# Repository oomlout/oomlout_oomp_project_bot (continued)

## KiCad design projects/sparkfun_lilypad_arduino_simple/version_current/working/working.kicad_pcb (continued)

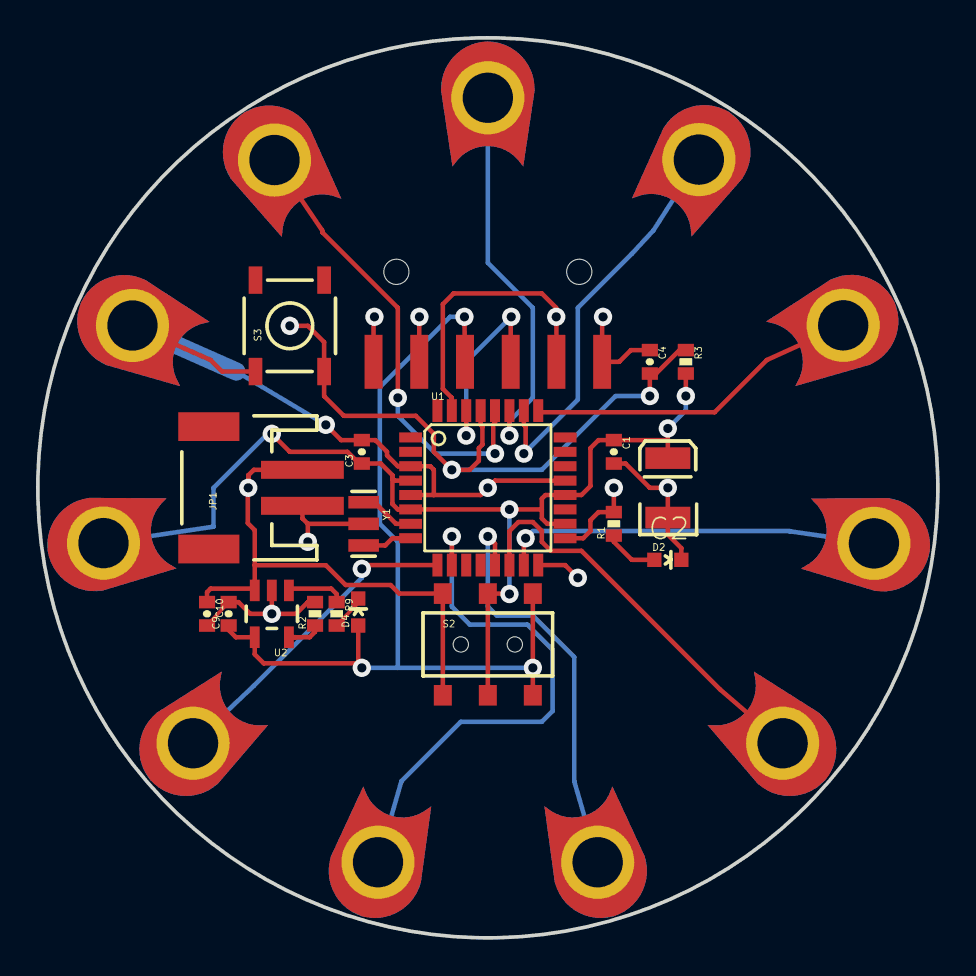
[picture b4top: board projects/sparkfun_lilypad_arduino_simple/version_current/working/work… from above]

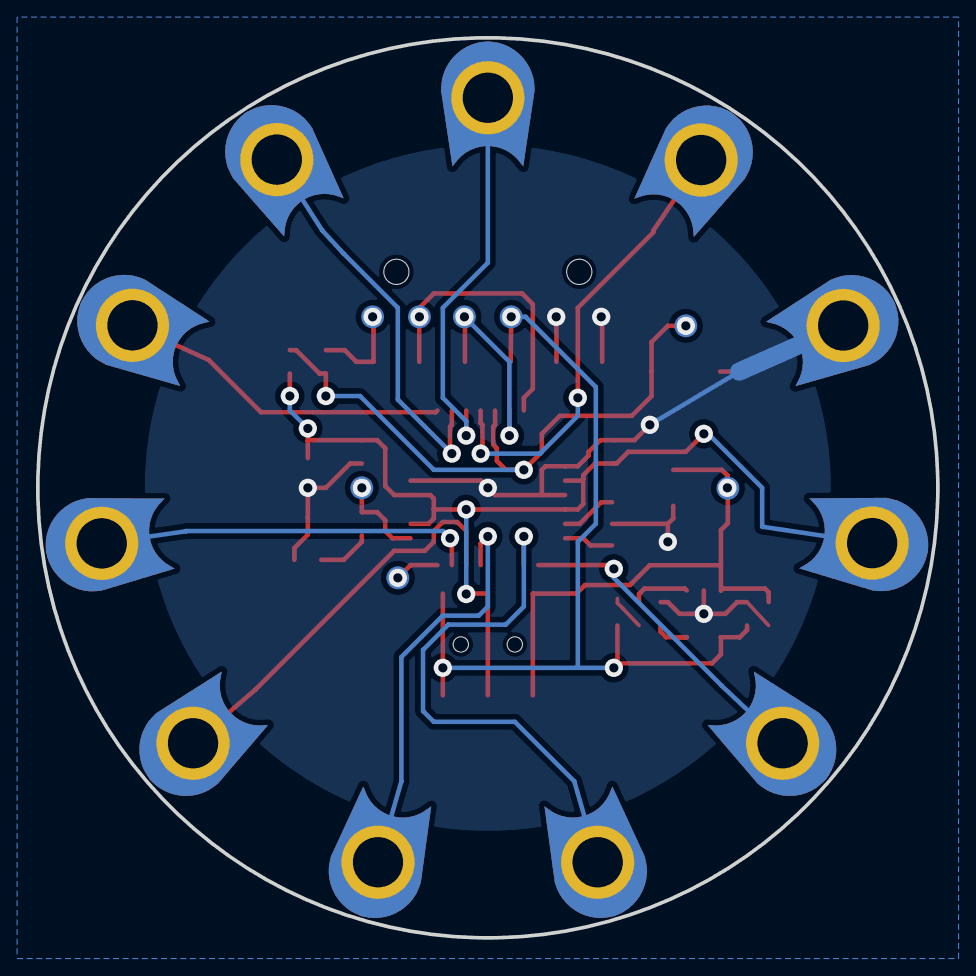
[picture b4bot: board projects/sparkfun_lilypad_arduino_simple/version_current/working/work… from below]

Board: 2 copper layers, 50.0 x 50.0 mm, 38 parts (8 on the bottom side), 25 nets.

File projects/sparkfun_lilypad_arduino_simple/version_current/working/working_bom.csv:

"Id";"Designator";"Footprint";"Quantity";"Designation";"Supplier and ref";
1;"Y1";"RESONATOR-SMD";1;"8MHz";;;
2;"A3/17,U$37,U$45,U$39,U$4,A4/18,U$41,A2/16,U$43,U$35,A5/19";"PETAL-LONG-1-2SIDE";11;"SEWTAP9";;;
3;"D2";"LED-0603";1;"Status";;;
4;"S2";"AYZ0202";1;"On/Off";;;
5;"C1,C4";"0402-CAP";2;"0.1uF";;;
6;"JP2";"1X06-SMD";1;"";;;
7;"U2";"SOT23-5";1;"MCP73831";;;
8;"D4";"LED-0603";1;"Yellow";;;
9;"C10,C9";"0402-CAP";2;"4.7uF";;;
10;"U1";"TQFP32-08";1;"ATMEGA328";;;
11;"JP1";"JST-2-SMD";1;"LiPo";;;
12;"R9,R1";"0402-RES";2;"330";;;
13;"C3";"0402-CAP";1;"1.0uF";;;
14;"R2";"0402-RES";1;"10k";;;
15;"S3";"TACTILE_SWITCH_SMD";1;"Reset";;;
16;"R3";"0402-RES";1;"10K";;;
17;"C2";"EIA3528";1;"47uF";;;
18;"TP-FTDI_VCC0,PP-MISO0,TP-DTR0,PP-RST0,TP-TX0,PP-SCK0,TP-VBATT0,TP-RX0";"PAD.03X.05";8;"";;;

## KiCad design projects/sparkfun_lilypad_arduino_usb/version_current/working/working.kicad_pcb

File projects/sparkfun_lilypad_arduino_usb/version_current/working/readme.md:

# OOMP Project  
## LilyPad_Arduino_USB  by sparkfun  
  
oomp key: oomp_projects_flat_sparkfun_lilypad_arduino_usb  
(snippet of original readme)  
  
LilyPad Arduino USB  
===================  
  
[    
*LilyPad Arduino USB (DEV-11990)*](https://www.sparkfun.com/products/11190)  
  
The LilyPad Arduino USB is a sewable Arduino compatible board with a built-in LiPo battery charger. It connects via microUSB cable to your computer, which means that, unlike regular LilyPad boards, it needs no external hardware to be programmed.   
  
As of Arduino release 1.0.2, the LilyPad Arduino USB is supported as a native board- no additional files needed!  
  
Firmware was compiled in WinAVR-20100110.    
Hardware was developed in EAGLE 6.3.0.  
  
License Information  
-------------------  
The hardware design is released under [CC-SA v3 license](http://creativecommons.org/licenses/by-sa/3.0/us/).  
  
The firmware is released under a modified beerware license, allowing for the purchase of any libation, alcoholic or non.  

  full source readme at [readme_src.md](readme_src.md)  
  
source repo at: [https://github.com/sparkfun/LilyPad_Arduino_USB](https://github.com/sparkfun/LilyPad_Arduino_USB)  
## Board  

## Schematic  

[schematic pdf](working_schematic.pdf)  
## Images

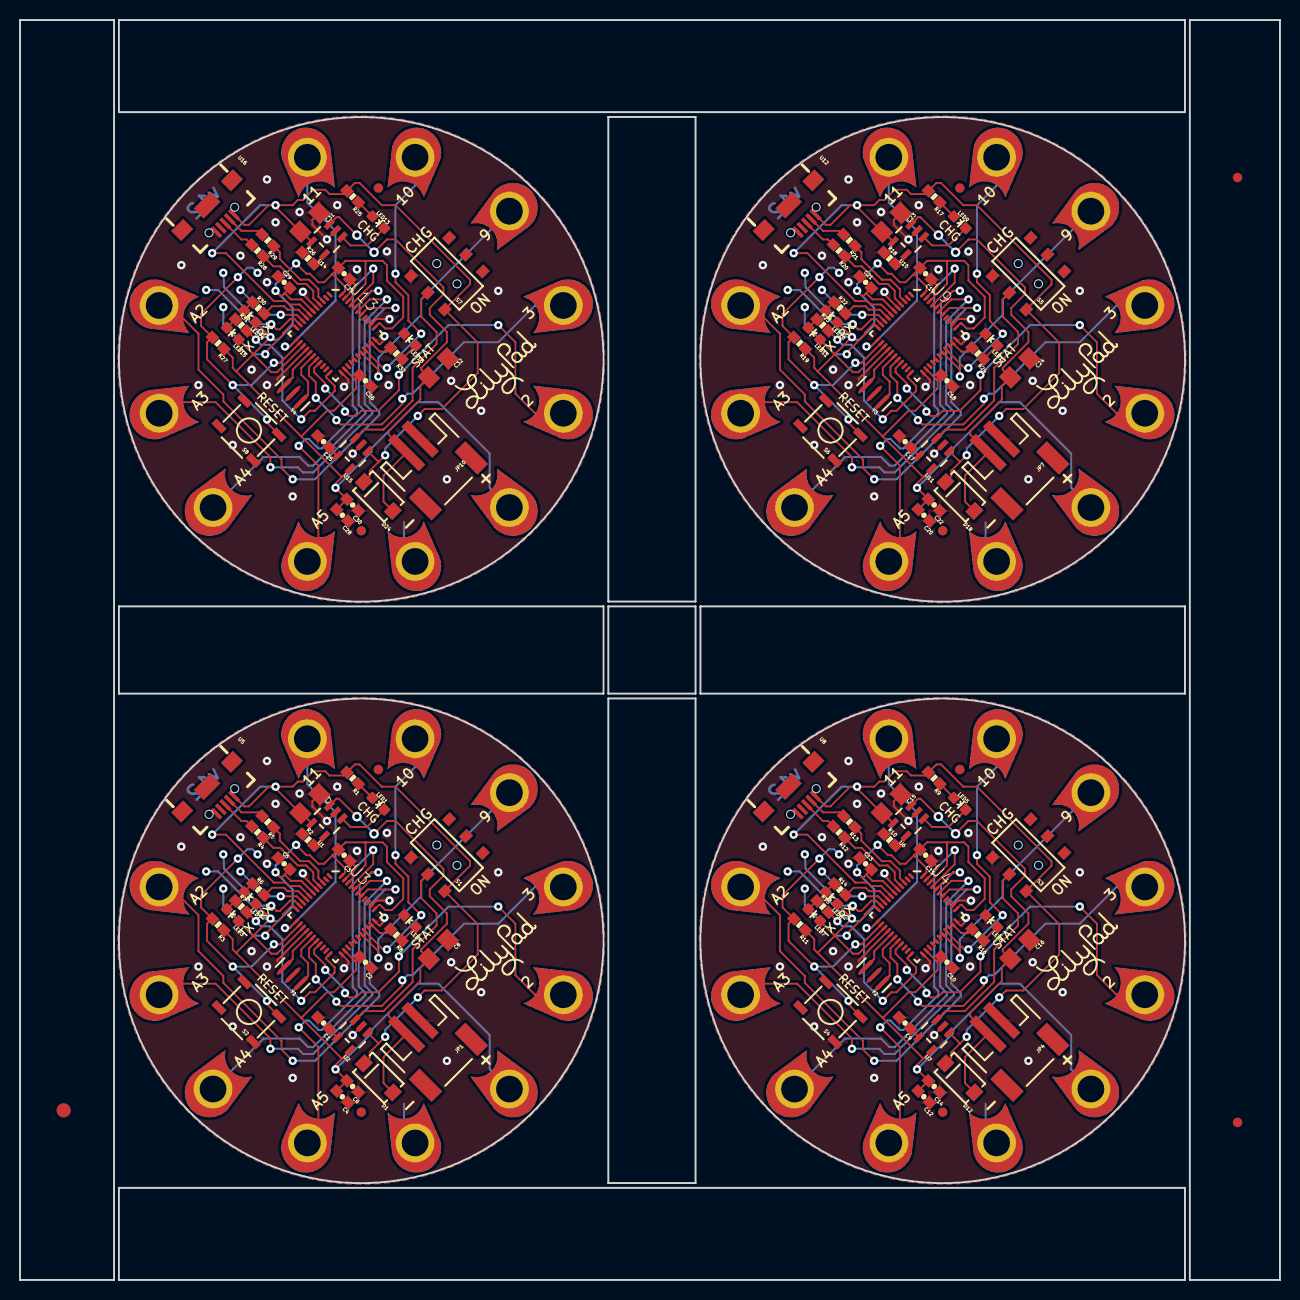
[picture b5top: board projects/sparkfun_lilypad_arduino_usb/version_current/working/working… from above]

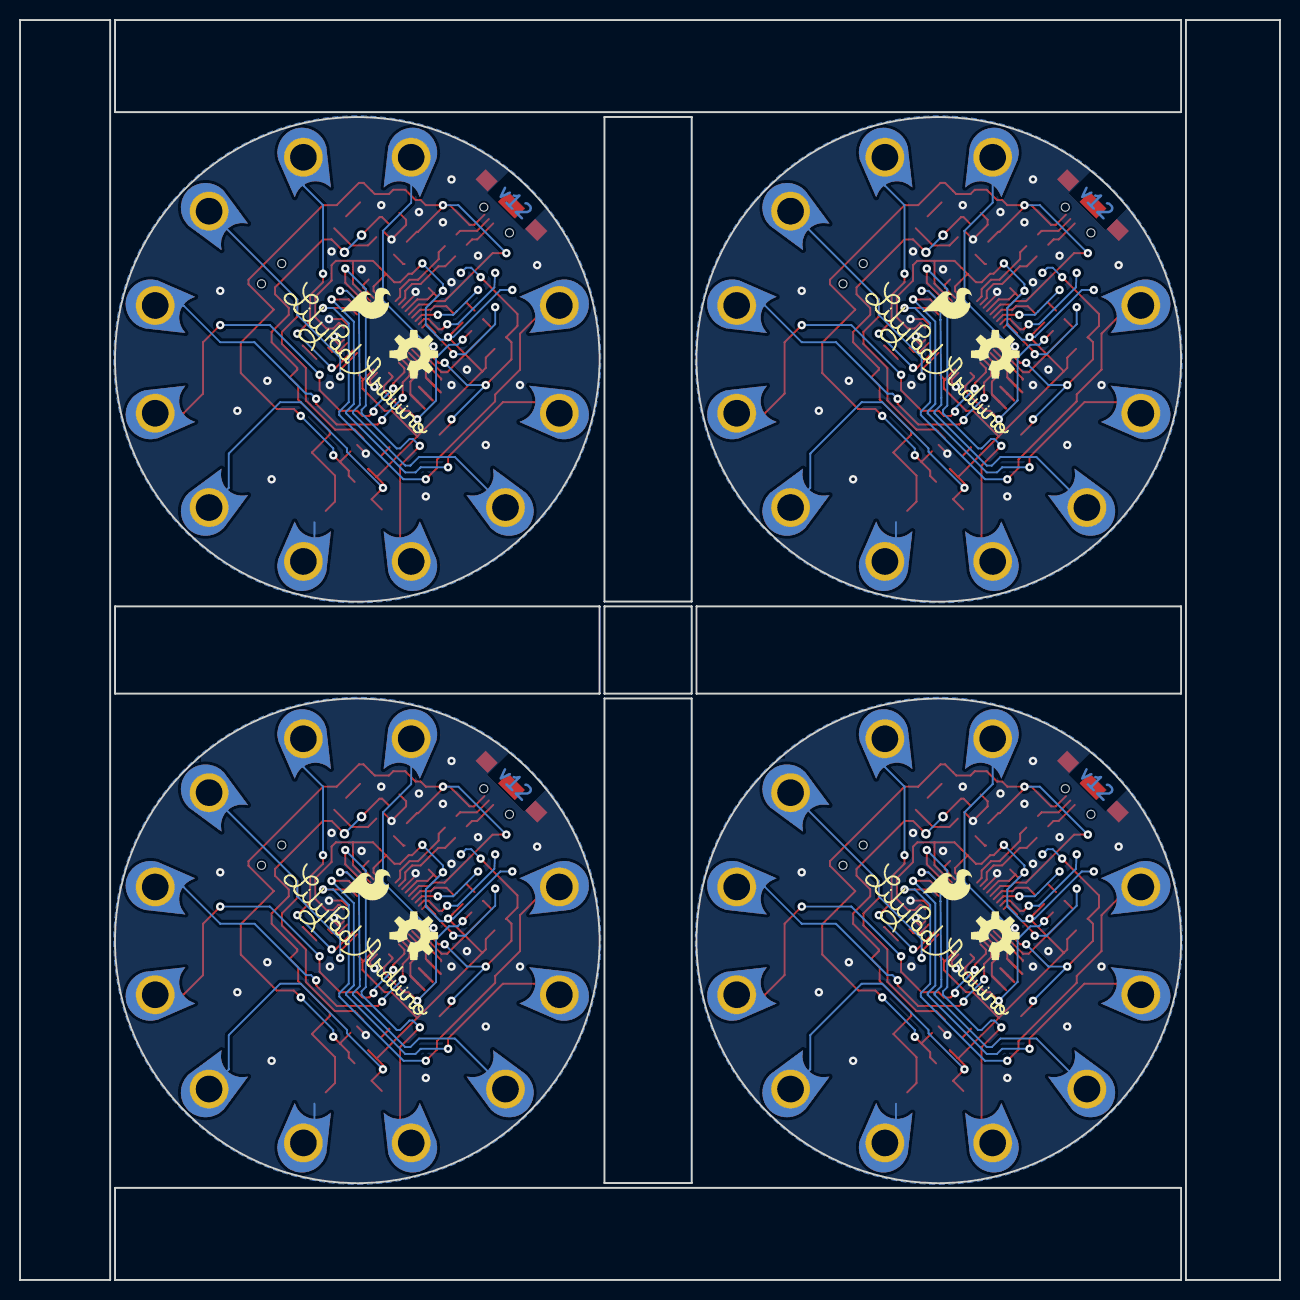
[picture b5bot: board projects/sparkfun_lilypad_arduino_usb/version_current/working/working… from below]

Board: 4 copper layers, 132.1 x 132.1 mm, 187 parts (12 on the bottom side), 124 nets.

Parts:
+0, +1, +2, +3: SEWTAP9; PETAL-LONG-1-2SIDE
-0, -1, -2, -3: SEWTAP9; PETAL-LONG-1-2SIDE
A1, A2, A3, A4, A5, A6, A7, A8, A9, A10, A11, A12, A13, A14, A15, A16: SEWTAP9; PETAL-LONG-1-2SIDE
C1, C9, C17, C25: 470pF; 0603-CAP
C2, C3, C4, C10, C11, C12, C18, C19, C20, C26, C27, C28: .1uF; 0603-CAP
C5, C13, C21, C29: 1uF; 0603-CAP
C6, C14, C22, C30: 4.7uF; 0603-CAP
C7, C8, C15, C16, C23, C24, C31, C32: 4.7uF; 1206
D1, D12, D18, D24: B340A; SMA-DIODE
D2, D3, D4, D5, D6, D7, D8, D9, D10, D11, D13, D14, D15, D16, D17, D19, D20, D21, D22, D23: SEWTAP9; PETAL-LONG-1-2SIDE
E$1: FIDUCIAL-1.5X3
E$3, E$5: FIDUCIAL-1X2
JP1, JP4, JP7, JP10: JST-2; JST-2-SMD
JP2, JP3, JP5, JP6, JP8, JP9, JP11, JP12: FIDUCIAL1X2; FIDUCIAL-1X2
LED1, LED2, LED3, LED4, LED5, LED6, LED7, LED8, LED9, LED10, LED11, LED12, LED13, LED14, LED15, LED16: RED; LED-0603
R1, R6, R7, R8, R9, R14, R15, R16, R17, R22, R23, R24, R25, R30, R31, R32: 330; 0603-RES
R2, R3, R10, R11, R18, R19, R26, R27: 10k; 0603-RES
R4, R5, R12, R13, R20, R21, R28, R29: 22; 0603-RES
S1, S3, S5, S7: DPDT; AYZ0202
S2, S4, S6, S8: !RESET; TACTILE_SWITCH_SMD
U1, U6, U10, U14: MCP73831; SOT23-5
U2, U7, U11, U15: MIC5219 3.3V; SOT23-5
U3, U4, U9, U13: ATMEGA32U41:1-LESS_PASTE; QFN-44-NOPAD_1_1-LESS_PASTE
U5, U8, U12, U16: USB-AB-MICRO-SMD_V03
U$1, U$3, U$9, U$14: LOGO-LPLPA; LOGO-LPA
U$2, U$8, U$12, U$13: LOGO-LPLP; LOGO-LILYPAD
U$4, U$5, U$10, U$15: OSHW-LOGOM; OSHW-LOGO-M
U$6, U$7, U$11, U$16: SFE_LOGO_FLAME_.2
Y1, Y2, Y3, Y4: 8MHZ; RESONATOR-SMD

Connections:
3.3V: +0.1, C2.2, C3.2, C4.2, C5.2, C6.2, LED2.A, LED3.A, R3.1, U2.5, U3.6, U3.14, U3.24, U3.34, U3.42, U3.44
3.3V1: +1.1, C10.2, C11.2, C12.2, C13.2, C14.2, LED6.A, LED7.A, R11.1, U4.6, U4.14, U4.24, U4.34, U4.42, U4.44, U7.5
3.3V2: +2.1, C18.2, C19.2, C20.2, C21.2, C22.2, LED10.A, LED11.A, R19.1, U9.6, U9.14, U9.24, U9.34, U9.42, U9.44, U11.5
3.3V3: +3.1, C26.2, C27.2, C28.2, C29.2, C30.2, LED14.A, LED15.A, R27.1, U13.6, U13.14, U13.24, U13.34, U13.42, U13.44, U15.5
5V: C7.2, D1.C, R1.2, S1.1, U1.4, U2.1, U3.7, U5.VBUS1
5V1: C15.2, D12.C, R9.2, S3.1, U4.7, U6.4, U7.1, U8.VBUS1
5V2: C23.2, D18.C, R17.2, S5.1, U9.7, U10.4, U11.1, U12.VBUS1
5V3: C31.2, D24.C, R25.2, S7.1, U13.7, U14.4, U15.1, U16.VBUS1
D+: R4.1, U3.4
D+1: R12.1, U4.4
D+2: R20.1, U9.4
D+3: R28.1, U13.4
D-: R5.1, U3.3
D-1: R13.1, U4.3
D-2: R21.1, U9.3
D-3: R29.1, U13.3
GND: -0.1, C1.2, C2.1, C3.1, C4.1, C5.1, C6.1, C7.1, C8.1, JP1.1, LED4.C, R2.1, S1.3, S2.1, U1.2, U2.2, U3.5, U3.15, U3.23, U3.33, U3.35, U3.43, U5.GND1, Y1.2
GND1: -1.1, C9.2, C10.1, C11.1, C12.1, C13.1, C14.1, C15.1, C16.1, JP4.1, LED8.C, R10.1, S3.3, S4.1, U4.5, U4.15, U4.23, U4.33, U4.35, U4.43, U6.2, U7.2, U8.GND1, Y2.2
GND2: -2.1, C17.2, C18.1, C19.1, C20.1, C21.1, C22.1, C23.1, C24.1, JP7.1, LED12.C, R18.1, S5.3, S6.1, U9.5, U9.15, U9.23, U9.33, U9.35, U9.43, U10.2, U11.2, U12.GND1, Y3.2
GND3: -3.1, C25.2, C26.1, C27.1, C28.1, C29.1, C30.1, C31.1, C32.1, JP10.1, LED16.C, R26.1, S7.3, S8.1, U13.5, U13.15, U13.23, U13.33, U13.35, U13.43, U14.2, U15.2, U16.GND1, Y4.2
unnamed: LED2.C, R6.1
unnamed: S1.2, U2.3
unnamed: LED1.A, R1.1
unnamed: LED1.C, U1.1
unnamed: U3.17, Y1.1
unnamed: R2.2, U1.5
unnamed: U3.16, Y1.3
unnamed: C1.1, U2.4
unnamed: D11.1, U3.12
unnamed: D10.1, U3.30
unnamed: D9.1, U3.29
unnamed: D5.1, U3.19
unnamed: D6.1, U3.18
unnamed: A5.1, U3.41
unnamed: A4.1, U3.40
unnamed: A3.1, U3.39
unnamed: A2.1, U3.38
unnamed: LED4.A, R8.1
unnamed: R5.2, U5.D-1
unnamed: R4.2, U5.D+1
unnamed: LED3.C, R7.1
unnamed: S3.2, U7.3
unnamed: LED5.A, R9.1
unnamed: LED5.C, U6.1
unnamed: R10.2, U6.5
unnamed: C9.1, U7.4
unnamed: D8.1, U4.12
unnamed: D7.1, U4.30
unnamed: D3.1, U4.29
unnamed: A7.1, U4.41
unnamed: A8.1, U4.40
unnamed: A6.1, U4.39
unnamed: A1.1, U4.38
unnamed: R13.2, U8.D-1
unnamed: R12.2, U8.D+1
unnamed: LED6.C, R14.1
unnamed: LED7.C, R15.1
unnamed: U4.17, Y2.1
unnamed: U4.16, Y2.3
unnamed: D2.1, U4.19
unnamed: D4.1, U4.18
unnamed: LED8.A, R16.1
unnamed: S5.2, U11.3
unnamed: LED9.A, R17.1
unnamed: LED9.C, U10.1
unnamed: R18.2, U10.5
unnamed: C17.1, U11.4
unnamed: D17.1, U9.12
unnamed: D16.1, U9.30
unnamed: D14.1, U9.29
unnamed: A11.1, U9.41
unnamed: A12.1, U9.40
unnamed: A10.1, U9.39
unnamed: A9.1, U9.38
unnamed: R21.2, U12.D-1
unnamed: R20.2, U12.D+1
unnamed: LED10.C, R22.1
unnamed: LED11.C, R23.1
unnamed: U9.17, Y3.1
unnamed: U9.16, Y3.3
unnamed: D13.1, U9.19
unnamed: D15.1, U9.18
unnamed: LED12.A, R24.1
unnamed: S7.2, U15.3
unnamed: LED13.A, R25.1
unnamed: LED13.C, U14.1
unnamed: R26.2, U14.5
unnamed: C25.1, U15.4
unnamed: D23.1, U13.12
unnamed: D22.1, U13.30
unnamed: D20.1, U13.29
unnamed: A15.1, U13.41
unnamed: A16.1, U13.40
unnamed: A14.1, U13.39
unnamed: A13.1, U13.38
unnamed: R29.2, U16.D-1
unnamed: R28.2, U16.D+1
unnamed: LED14.C, R30.1
unnamed: LED15.C, R31.1
unnamed: U13.17, Y4.1
unnamed: U13.16, Y4.3
unnamed: D19.1, U13.19
unnamed: D21.1, U13.18
unnamed: LED16.A, R32.1
RESET: R3.2, S2.3, U3.13
RESET1: R11.2, S4.3, U4.13
RESET2: R19.2, S6.3, U9.13
RESET3: R27.2, S8.3, U13.13
RX_LED: R6.2, U3.8
RX_LED1: R14.2, U4.8
RX_LED2: R22.2, U9.8
RX_LED3: R30.2, U13.8
TX_LED: R7.2, U3.22
TX_LED1: R15.2, U4.22
TX_LED2: R23.2, U9.22
TX_LED3: R31.2, U13.22
USER_LED: R8.2, U3.32
USER_LED1: R16.2, U4.32
USER_LED2: R24.2, U9.32
USER_LED3: R32.2, U13.32
V_BATT: C8.2, D1.A, JP1.2, U1.3
V_BATT1: C16.2, D12.A, JP4.2, U6.3
V_BATT2: C24.2, D18.A, JP7.2, U10.3
V_BATT3: C32.2, D24.A, JP10.2, U14.3

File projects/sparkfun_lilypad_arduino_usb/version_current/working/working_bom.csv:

"Id";"Designator";"Footprint";"Quantity";"Designation";"Supplier and ref";
1;"R23,R8,R24,R25,R31,R7,R6,R14,R22,R9,R15,R1,R32,R17,R30,R16";"0603-RES";16;"330";;;
2;"LED8,LED5,LED15,LED3,LED2,LED10,LED4,LED6,LED13,LED14,LED9,LED11,LED1,LED16,LED12,LED7";"LED-0603";16;"RED";;;
3;"A13,D23,D10,A7,D17,D5,-3,+1,+0,A3,D6,-0,A9,A10,D4,-2,D13,A16,D8,+3,D19,A1,A2,A12,A5,A6,A4,D16,D15,A11,D3,-1,D7,D2,D11,+2,D21,D14,D22,A8,A15,D9,D20,A14";"PETAL-LONG-1-2SIDE";44;"SEWTAP9";;;
4;"JP1,JP4,JP10,JP7";"JST-2-SMD";4;"JST-2";;;
5;"JP9,JP8,JP5,JP2,JP6,JP3,JP11,JP12";"FIDUCIAL-1X2";8;"FIDUCIAL1X2";;;
6;"C32,C7,C16,C23,C15,C8,C31,C24";"1206";8;"4.7uF";;;
7;"C10,C28,C4,C3,C27,C20,C12,C26,C2,C18,C11,C19";"0603-CAP";12;".1uF";;;
8;"S8,S6,S4,S2";"TACTILE_SWITCH_SMD";4;"!RESET";;;
9;"C22,C6,C14,C30";"0603-CAP";4;"4.7uF";;;
10;"U$13,U$2,U$12,U$8";"LOGO-LILYPAD";4;"LOGO-LPLP";;;
11;"R20,R13,R12,R5,R21,R28,R29,R4";"0603-RES";8;"22";;;
12;"D24,D12,D1,D18";"SMA-DIODE";4;"B340A";;;
13;"C29,C5,C21,C13";"0603-CAP";4;"1uF";;;
14;"U8,U5,U12,U16";"USB-AB-MICRO-SMD_V03";4;"";;;
15;"R18,R2,R19,R10,R3,R11,R27,R26";"0603-RES";8;"10k";;;
16;"E$3,E$5";"FIDUCIAL-1X2";2;"";;;
17;"U7,U15,U11,U2";"SOT23-5";4;"MIC5219 3.3V";;;
18;"S1,S3,S7,S5";"AYZ0202";4;"DPDT";;;
19;"C9,C25,C17,C1";"0603-CAP";4;"470pF";;;
20;"U13,U9,U3,U4";"QFN-44-NOPAD_1_1-LESS_PASTE";4;"ATMEGA32U41:1-LESS_PASTE";;;
21;"U1,U10,U6,U14";"SOT23-5";4;"MCP73831";;;
22;"E$1";"FIDUCIAL-1.5X3";1;"";;;
23;"Y1,Y3,Y2,Y4";"RESONATOR-SMD";4;"8MHZ";;;
24;"U$6,U$16,U$7,U$11";"SFE_LOGO_FLAME_.2";4;"";;;
25;"U$4,U$5,U$15,U$10";"OSHW-LOGO-M";4;"OSHW-LOGOM";;;
26;"U$14,U$3,U$1,U$9";"LOGO-LPA";4;"LOGO-LPLPA";;;

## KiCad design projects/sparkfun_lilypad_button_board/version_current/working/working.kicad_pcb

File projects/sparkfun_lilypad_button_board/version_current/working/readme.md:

# OOMP Project  
## LilyPad_Button_Board  by sparkfun  
  
oomp key: oomp_projects_flat_sparkfun_lilypad_button_board  
(snippet of original readme)  
  
SparkFun LilyPad Button Board  
========================================  

[*SparkFun LilyPad Button Board (DEV-08776)*](https://www.sparkfun.com/products/8776)  
  
We designed this board to give the user a low profile button without any sharp edges.   
Button closes when you push it and opens when you release (momentary push button).  
  
Repository Contents  
-------------------  
* **/Hardware** - All Eagle design files (.brd, .sch)  
  
Documentation  
-------------------  
* **[Hookup Guide](https://learn.sparkfun.com/tutorials/lilypad-buttons-and-switches)**  
  
License Information  
-------------------  
  
This product is _**open source**_!   
  
Please review the LICENSE.md file for license information.   
  
If you have any questions or concerns on licensing, please contact techsupport@sparkfun.com.  
  
Distributed as-is; no warranty is given.  
  
- Your friends at SparkFun.  
  
_<COLLABORATION CREDIT>_  
  
_Note: A portion of this sale is given back to Dr. Leah Buechley for continued development and education of e-textiles._  
  
  full source readme at [readme_src.md](readme_src.md)  
  
source repo at: [https://github.com/sparkfun/LilyPad_Button_Board](https://github.com/sparkfun/LilyPad_Button_Board)  
## Board  

## Schematic  

[schematic pdf](working_schematic.pdf)  
## Images

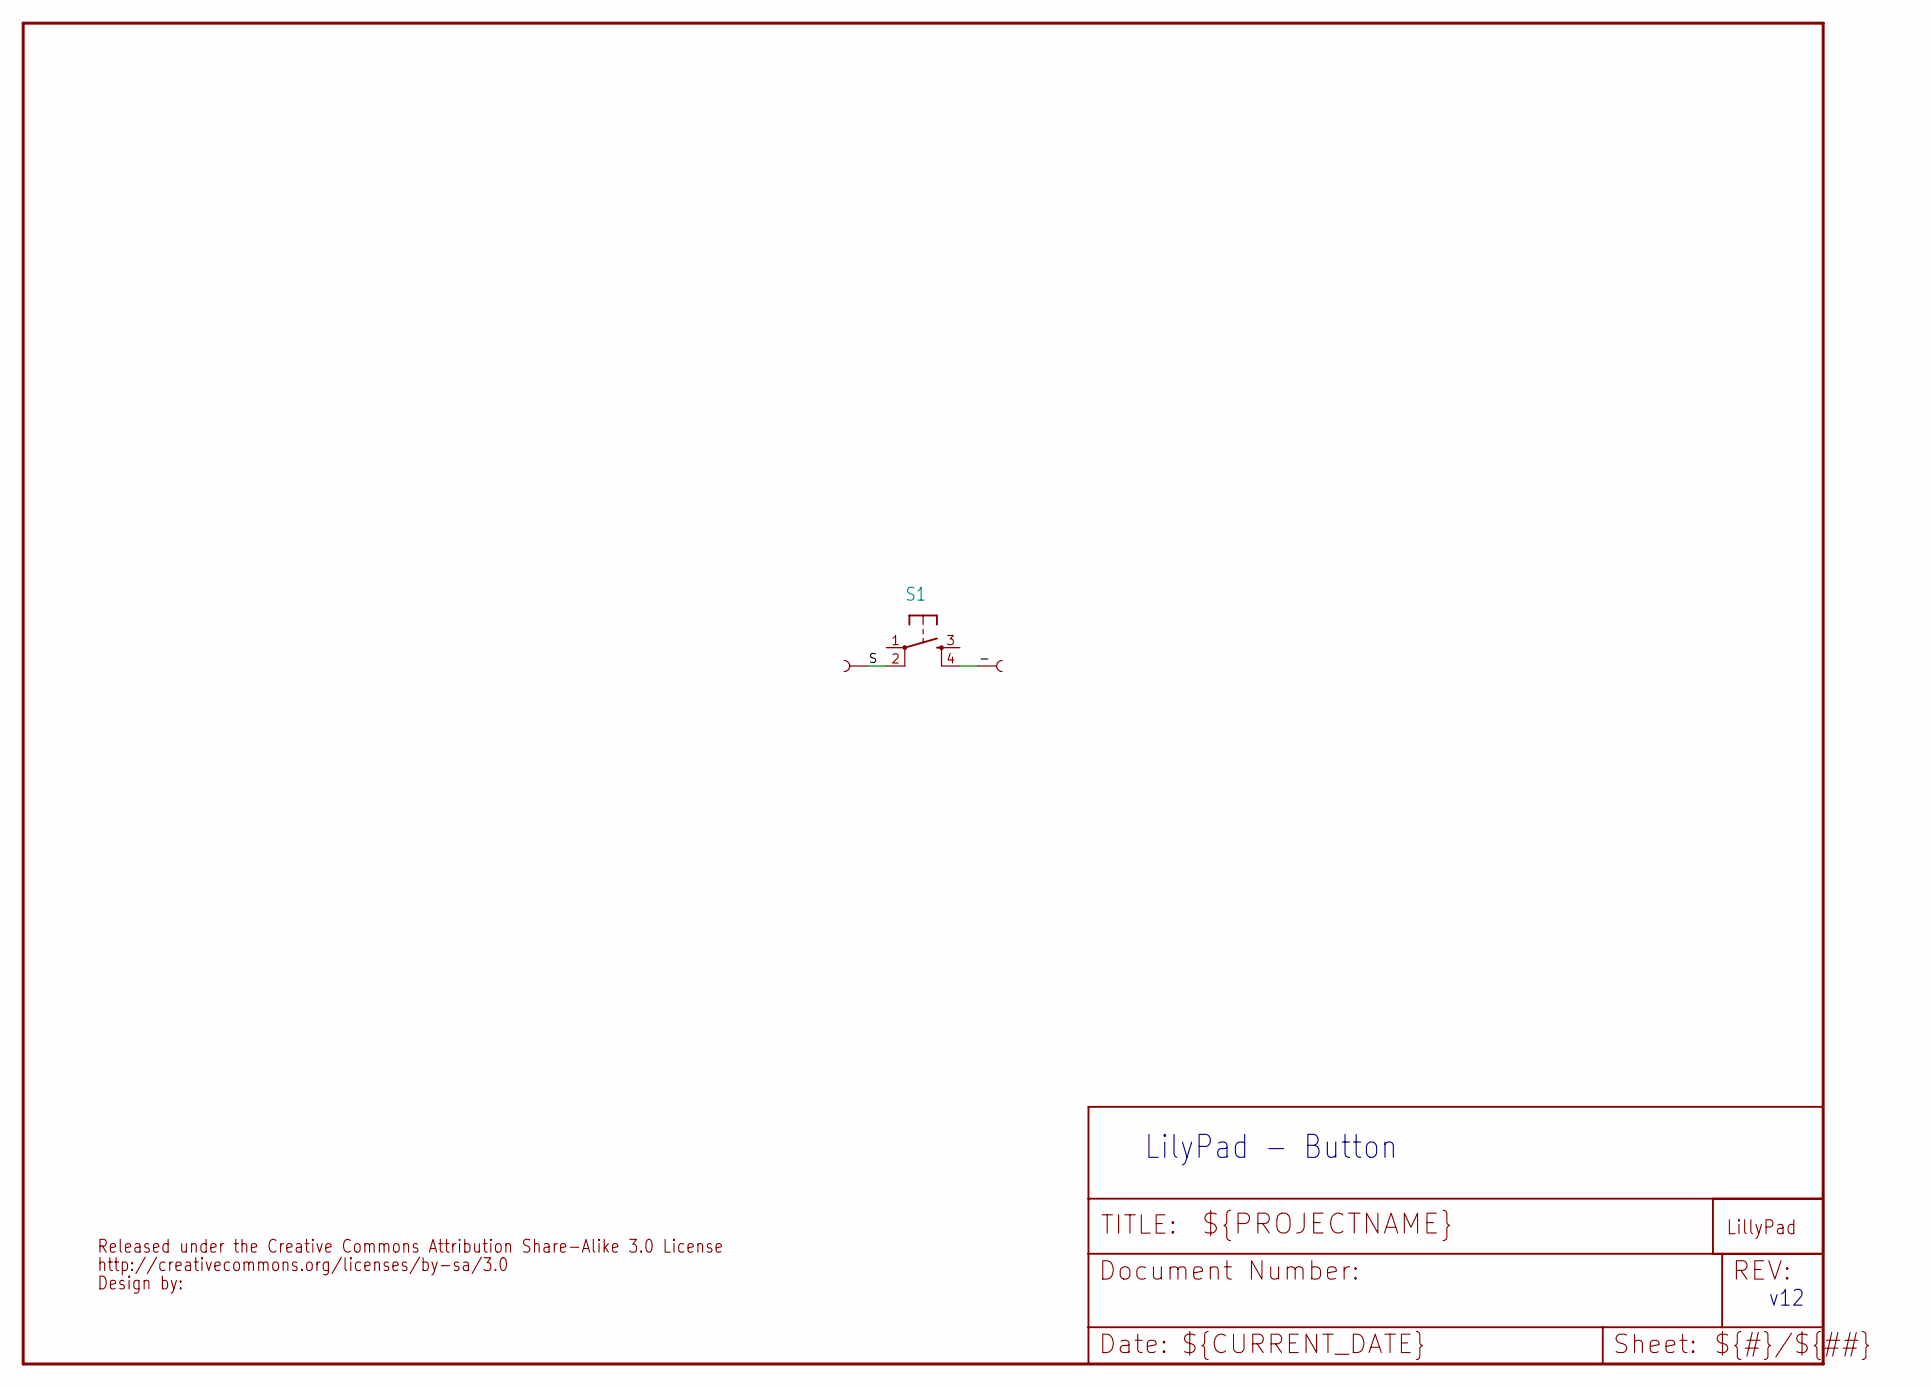
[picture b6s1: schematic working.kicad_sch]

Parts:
BUTTON-0: SEWTAP8; PETAL-MEDIUM-2SIDE
BUTTONS0: SEWTAP8; PETAL-MEDIUM-2SIDE
LOGO1: LOGO-LPL; LOGO-L
S1: TAC_SWITCHSMD; TACTILE_SWITCH_SMD
U$1: CREATIVE_COMMONS

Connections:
-: BUTTON-0.1, S1.4
S: BUTTONS0.1, S1.2

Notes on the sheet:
v12
LilyPad - Button

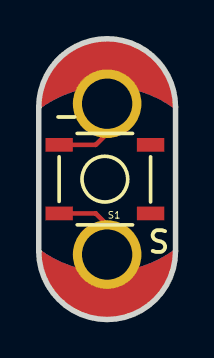
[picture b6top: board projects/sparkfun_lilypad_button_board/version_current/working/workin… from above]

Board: 2 copper layers, 7.6 x 15.6 mm, 5 parts (1 on the bottom side), 2 nets.

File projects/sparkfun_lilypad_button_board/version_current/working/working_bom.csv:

Row,Description,Part,References,Value,Footprint,Quantity Per PCB,Status,Datasheet
1,,SEWTAP8,BUTTON-0 BUTTONS0,SEWTAP8,PETAL-MEDIUM-2SIDE,2, ,
2,,LOGO-LPL,LOGO1,LOGO-LPL,LOGO-L,1, ,
3,,TAC_SWITCHSMD,S1,TAC_SWITCHSMD,TACTILE_SWITCH_SMD,1, ,
4,,CREATIVE_COMMONS,U$1,CREATIVE_COMMONS,CREATIVE_COMMONS,1, ,





Project info:
Schematic:,working
Variant:,default
Revision:,
Date:,2023-08-06_12-56-04
KiCad Version:,7.0.6-7.0.6~ubuntu22.04.1
Statistics:
Component Groups:,4
Component Count:,5 (0 SMD/ 0 THT)
Fitted Components:,5 (0 SMD/ 0 THT)
Number of PCBs:,1
Total Components:,5

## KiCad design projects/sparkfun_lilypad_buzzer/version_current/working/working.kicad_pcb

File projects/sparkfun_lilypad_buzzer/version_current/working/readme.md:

# OOMP Project  
## LilyPad_Buzzer  by sparkfun  
  
oomp key: oomp_projects_flat_sparkfun_lilypad_buzzer  
(snippet of original readme)  
  
LilyPad Buzzer  
========================================  

[*LilyPad Buzzer (DEV-08463)*](https://www.sparkfun.com/products/8463)  
  
This is a small buzzer for the LilyPad system.   
Use 2 I/O pins on the LilyPad main board and create different noises based on the different frequency of I/O toggling.   
Loud enough to hear inside a pocket but not obtrusively loud.  
  
Repository Contents  
-------------------  
  
* **/Hardware** - Eagle design files (.brd, .sch)  
* **/Production** - Production panel files (.brd)  
  
Documentation  
--------------  
* **[SparkFun Fritzing repo](https://github.com/sparkfun/Fritzing_Parts)** - Fritzing diagrams for SparkFun products.  
* **[SparkFun 3D Model repo](https://github.com/sparkfun/3D_Models)** - 3D models of SparkFun products.   

License Information  
-------------------  
This product is _**open source**_!   
  
The **hardware** is released under [Creative Commons ShareAlike 4.0 International](https://creativecommons.org/licenses/by-sa/4.0/).  
  
Please use, reuse, and modify these files as you see fit. Please maintain attribution to SparkFun Electronics and release anything derivative under the same license.  
  
Distributed as-is; no warranty is given.  
  
- Your friends at SparkFun.  
  
_**Note**: A portion of this sale is given back to Dr. Leah Buechley for continued development and education of e-textiles._  

  full source readme at [readme_src.md](readme_src.md)  
  
source repo at: [https://github.com/sparkfun/LilyPad_Buzzer](https://github.com/sparkfun/LilyPad_Buzzer)  
## Board  

## Schematic  

[schematic pdf](working_schematic.pdf)  
## Images

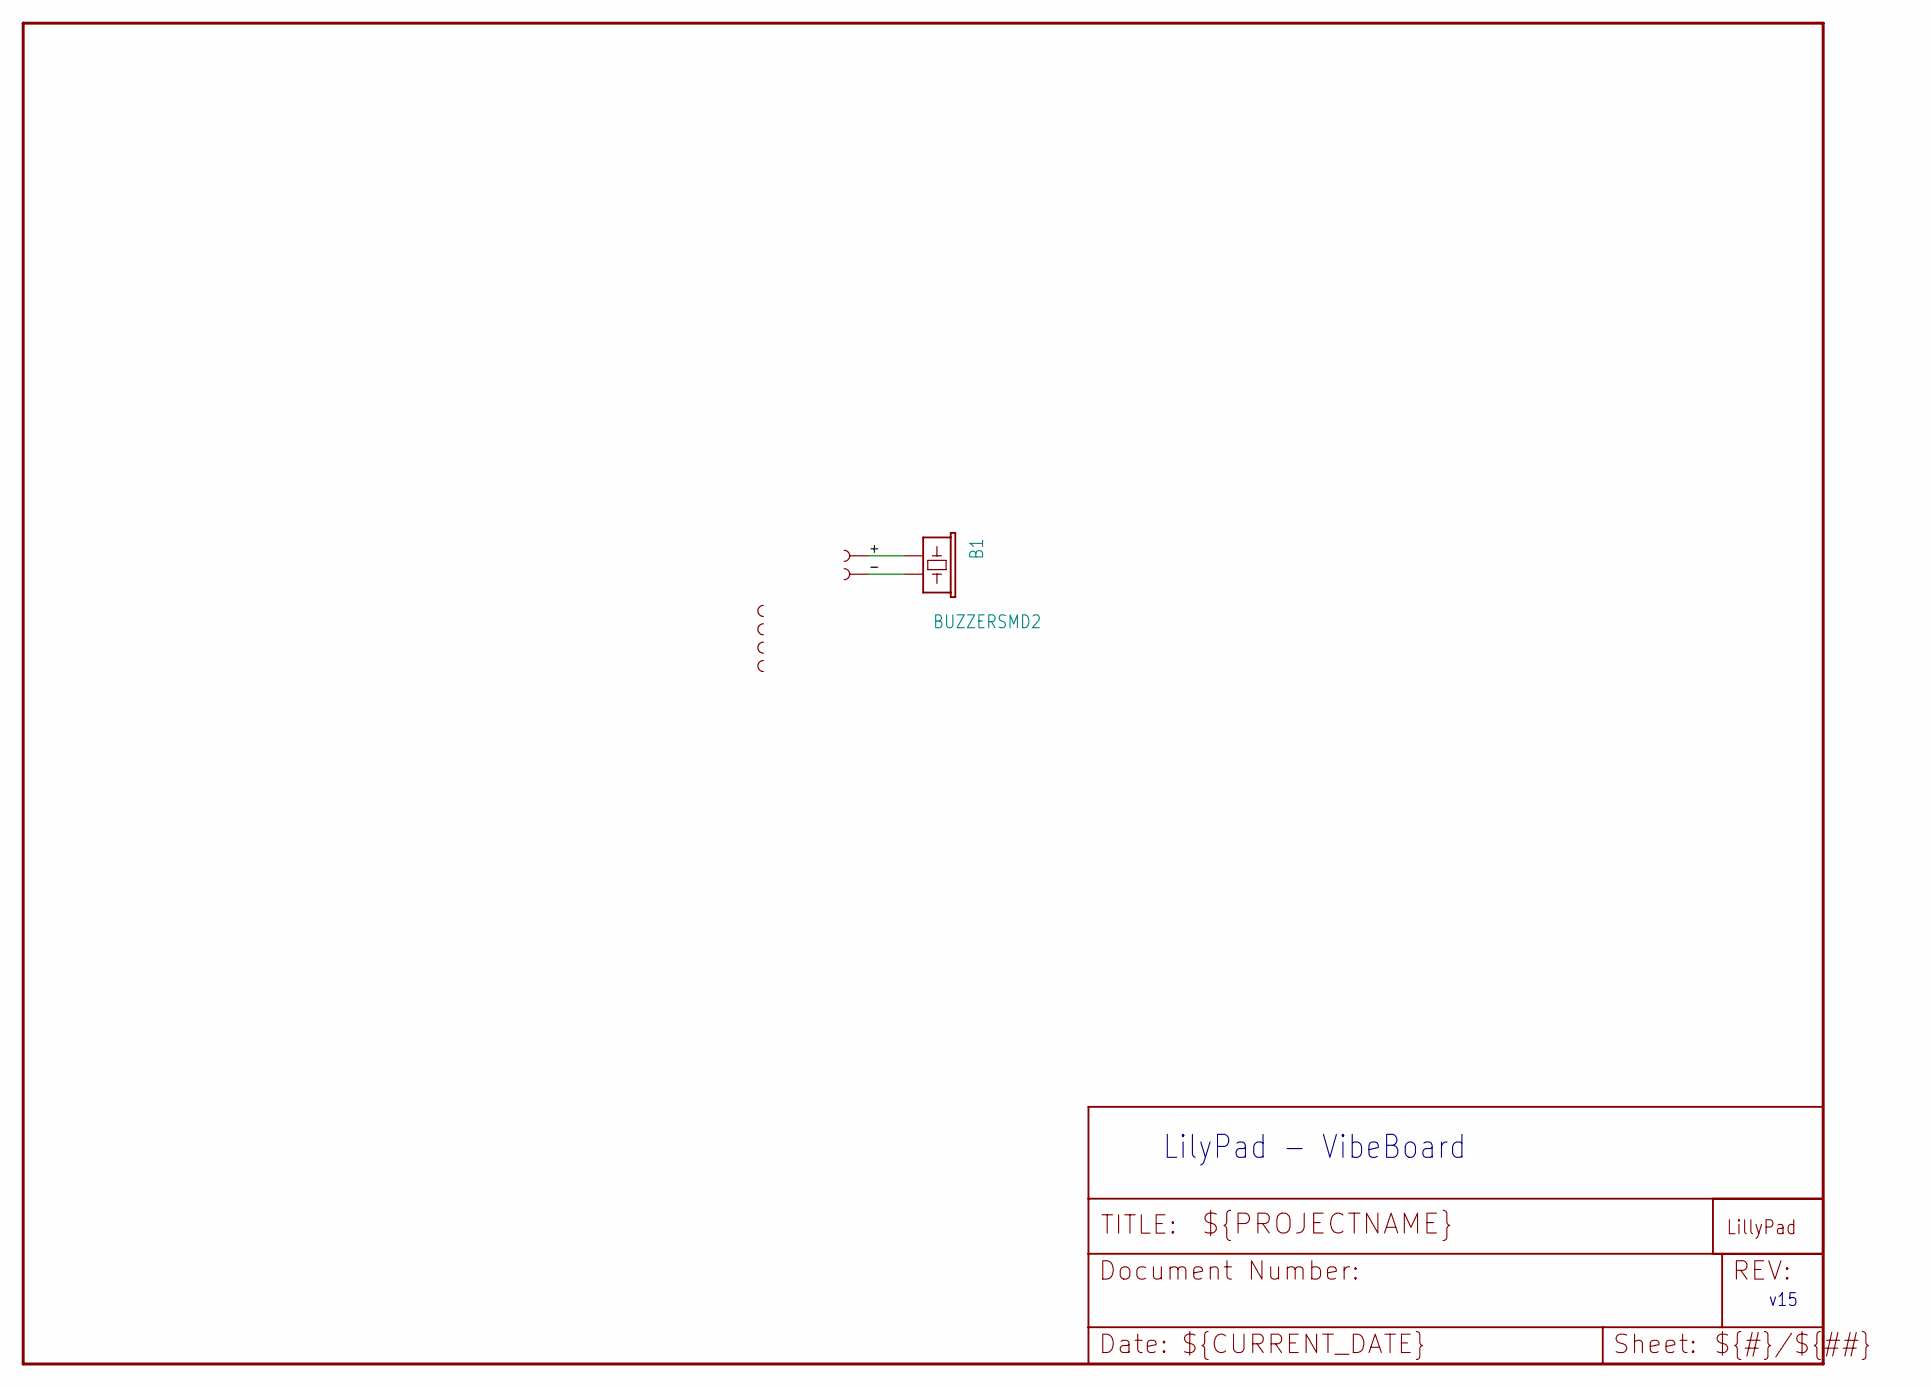
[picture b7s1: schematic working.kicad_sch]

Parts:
B1: BUZZERSMD2; BUZZER-CCV
U$1, U$4, U$6, U$7: SEWTAP-NOHOLE2; PETAL-NOHOLE-2SIDE
U$2: LOGO-LPLP; LOGO-LILYPAD
U$8, U$9: SEWTAP6; PETAL-SMALL-2SIDE

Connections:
+: B1.+ (1), U$9.1
-: B1.- (2), U$8.1

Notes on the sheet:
v15
LilyPad - VibeBoard

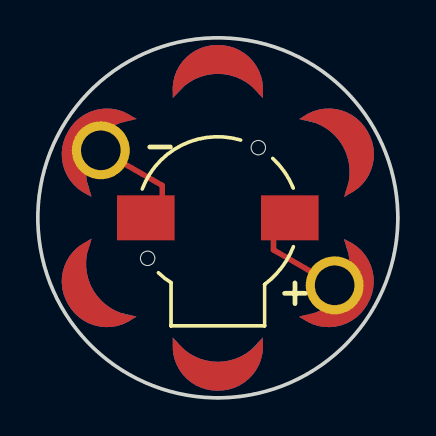
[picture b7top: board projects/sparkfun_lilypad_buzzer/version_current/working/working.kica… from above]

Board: 2 copper layers, 20.0 x 20.0 mm, 8 parts (1 on the bottom side), 2 nets.
